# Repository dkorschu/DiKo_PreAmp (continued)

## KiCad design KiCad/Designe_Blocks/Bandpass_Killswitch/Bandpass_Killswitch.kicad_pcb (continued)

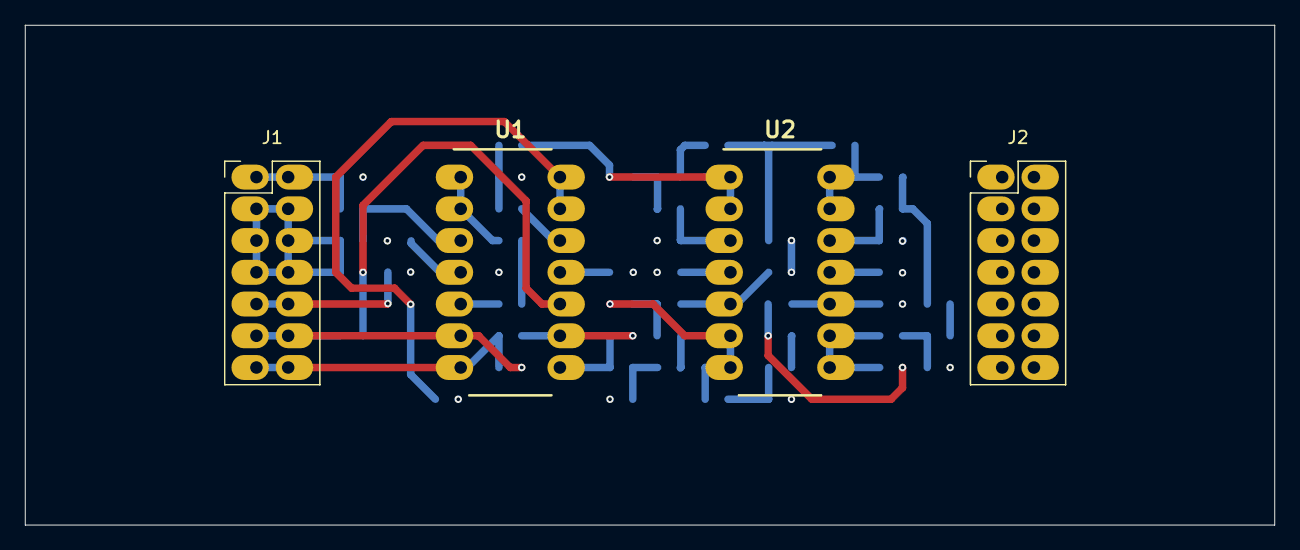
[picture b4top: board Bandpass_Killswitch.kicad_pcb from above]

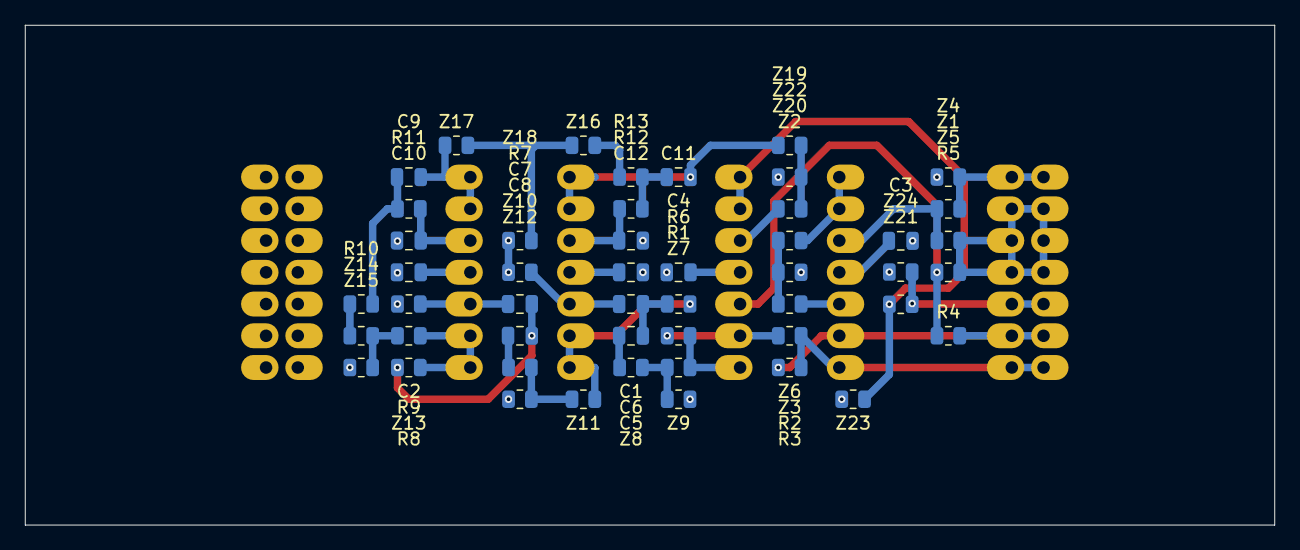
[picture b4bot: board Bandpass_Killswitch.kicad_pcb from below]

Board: 4 copper layers, 100.0 x 40.0 mm, 53 parts (49 on the bottom side), 37 nets.

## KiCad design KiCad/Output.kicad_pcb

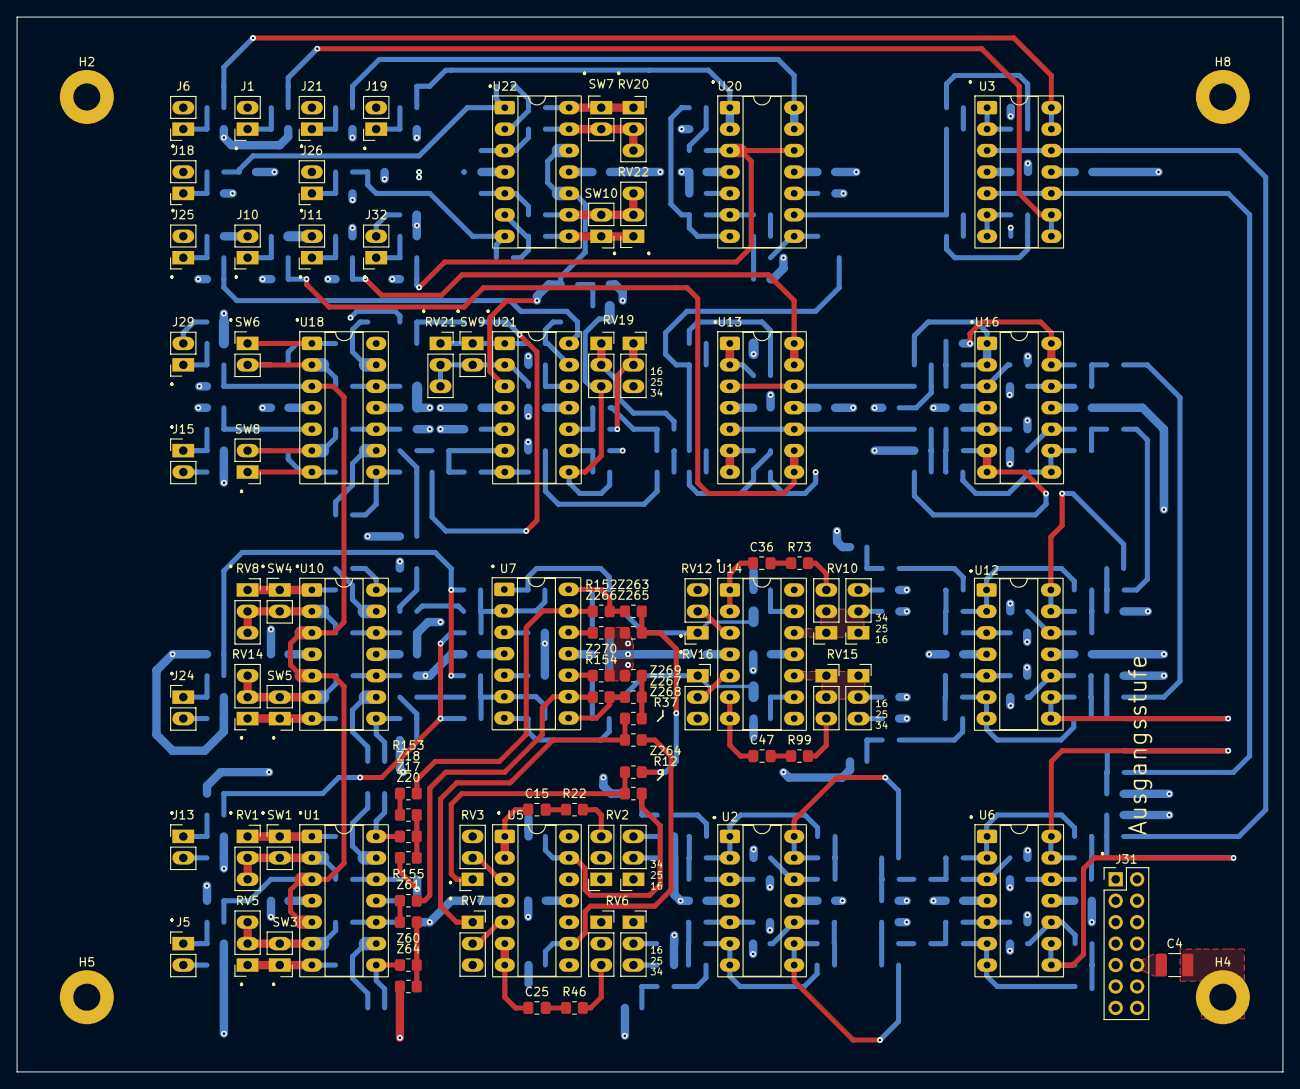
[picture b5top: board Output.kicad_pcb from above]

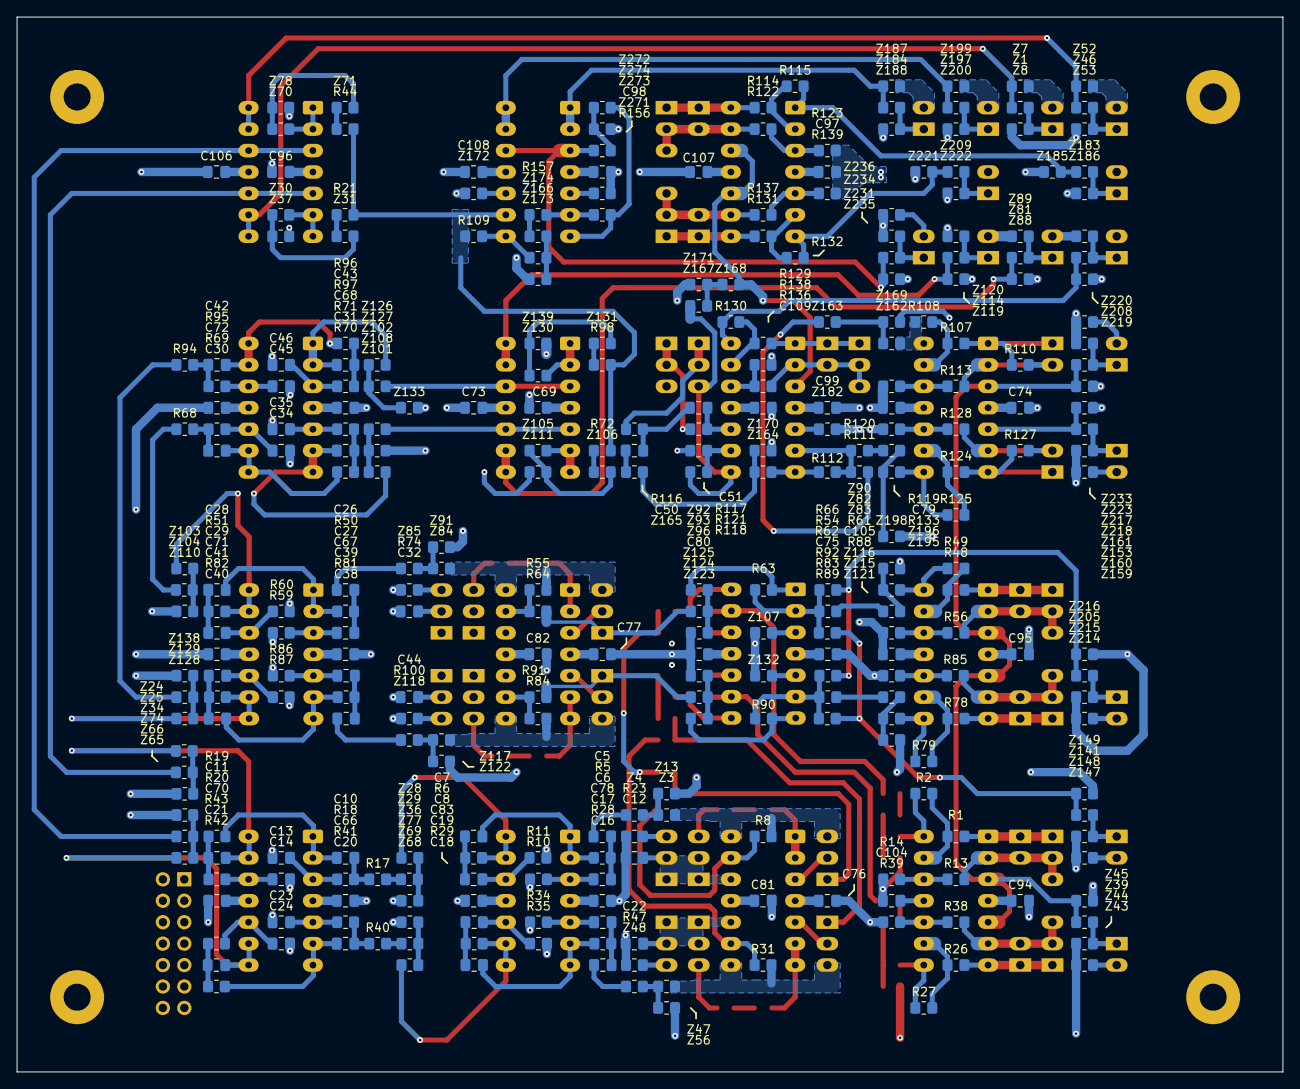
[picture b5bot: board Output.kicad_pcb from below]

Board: 4 copper layers, 150.0 x 125.0 mm, 393 parts (304 on the bottom side), 253 nets.

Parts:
C4: 10n; C_1210_3225Metric_Pad1.33x2.70mm_HandSolder
C5, C6, C7, C8, C10, C11, C13, C14, C16, C17, C18, C19, C20, C21, C23, C24, C26, C27, C28, C29, C30, C31, C34, C35, C38, C39, C40, C41, C42, C43, C45, C46: 130n; C_0805_2012Metric_Pad1.18x1.45mm_HandSolder
C12, C22, C32, C44: 470p; C_0805_2012Metric_Pad1.18x1.45mm_HandSolder
C15, C25, C36, C47: 3n; C_0805_2012Metric_Pad1.18x1.45mm_HandSolder
C50, C51: 6n8; C_0805_2012Metric_Pad1.18x1.45mm_HandSolder
C66, C67, C68, C69, C70, C71, C72, C73, C74, C75, C76, C77, C78, C79, C80, C81, C82, C83, C94, C95, C96, C97, C98, C99, C104, C105, C106, C107, C108, C109: 100n; C_0805_2012Metric_Pad1.18x1.45mm_HandSolder
H2, H5, H8: MountingHole; MountingHole_3.2mm_M3_Pad
H4: MountingHole_Pad; MountingHole_3.2mm_M3_Pad
J1: Bass_Out; PinSocket_1x02_P2.54mm_Vertical_LongPads
J5: Phono/Line_In; PinHeader_1x02_P2.54mm_Vertical_LongPads
J6: Kick_Out; PinSocket_1x02_P2.54mm_Vertical_LongPads
J10: Mid_Out; PinSocket_1x02_P2.54mm_Vertical_LongPads
J11: High_Out; PinSocket_1x02_P2.54mm_Vertical_LongPads
J13, J15, J24: Mic_Effekt_In; PinHeader_1x02_P2.54mm_Vertical_LongPads
J18: AUX_Send_1; PinSocket_1x02_P2.54mm_Vertical_LongPads
J19: Line_Out_L; PinSocket_1x02_P2.54mm_Vertical_LongPads
J21: Line_Out_R; PinSocket_1x02_P2.54mm_Vertical_LongPads
J25: AUX_Send_3; PinSocket_1x02_P2.54mm_Vertical_LongPads
J26: AUX_Send_2; PinSocket_1x02_P2.54mm_Vertical_LongPads
J29, J32: Pegel_Out; PinSocket_1x02_P2.54mm_Vertical_LongPads
J31: Conn_02x07_Odd_Even; PinHeader_2x07_P2.54mm_Vertical
R1, R26, R48, R78, R114, R129, R131: 4k7; R_0805_2012Metric_Pad1.20x1.40mm_HandSolder
R2, R21, R27, R44, R49, R54, R62, R63, R66, R72, R79, R83, R89, R90, R92, R98, R107, R108, R109, R111, R112, R115, R116, R117, R118, R120, R121, R124, R125, R130, R132, R152, R153, R154, R155, R156, R157: 10k; R_0805_2012Metric_Pad1.20x1.40mm_HandSolder
R5, R6, R10, R11, R22, R23, R28, R29, R34, R35, R46, R47, R50, R51, R59, R60, R73, R74, R81, R82, R86, R87, R99, R100: 6k8; R_0805_2012Metric_Pad1.20x1.40mm_HandSolder
R8, R12, R17, R18, R19, R20, R31, R37, R40, R41, R42, R43, R55, R64, R68, R69, R70, R71, R84, R91, R94, R95, R96, R97: 22k; R_0805_2012Metric_Pad1.20x1.40mm_HandSolder
R13, R38, R56, R85, R122, R136, R137: 470R; R_0805_2012Metric_Pad1.20x1.40mm_HandSolder
R14, R39, R61, R88, R123, R138, R139: 1k; R_0805_2012Metric_Pad1.20x1.40mm_HandSolder
R110, R113, R119, R127, R128, R133: 5k; R_0805_2012Metric_Pad1.20x1.40mm_HandSolder
RV1, RV5, RV8, RV14, RV20, RV21, RV22: 50k log; PinSocket_1x03_P2.54mm_Vertical_LongPads
RV2, RV10: 220k log; PinSocket_2x03_P2.54mm_Vertical_LongPads_Mirrored
RV3, RV7, RV12, RV16: 47k lin; PinSocket_1x03_P2.54mm_Vertical_LongPads
RV6, RV15, RV19: 220k log; PinSocket_2x03_P2.54mm_Vertical_LongPads
SW1, SW3, SW4, SW5, SW6, SW7, SW8, SW9, SW10: SW_SPDT; PinHeader_1x02_P2.54mm_Vertical_LongPads
U1, U2, U3, U5, U6, U7, U10, U12, U13, U14, U16, U18, U20, U21, U22: TL074; DIP-14_W7.62mm_Socket_LongPads
Z1, Z3, Z4, Z7, Z8, Z13, Z17, Z18, Z20, Z24, Z25, Z28, Z29, Z30, Z31, Z34, Z36, Z37, Z39, Z43, Z44, Z45, Z46, Z47, Z48, Z52, Z53, Z56, Z60, Z61, Z64, Z65, Z66, Z68, Z69, Z70, Z71, Z74, Z77, Z78, Z81, Z82, Z83, Z84, Z85, Z88, Z89, Z90, Z91, Z92, Z93, Z96, Z101, Z102, Z103, Z104, Z105, Z106, Z107, Z108, Z110, Z111, Z114, Z115, Z116, Z117, Z118, Z119, Z120, Z121, Z122, Z123, Z124, Z125, Z126, Z127, Z128, Z129, Z130, Z131, Z132, Z133, Z138, Z139, Z141, Z147, Z148, Z149, Z153, Z159, Z160, Z161, Z162, Z163, Z164, Z165, Z166, Z167, Z168, Z169, Z170, Z171, Z172, Z173, Z174, Z182, Z183, Z184, Z185, Z186, Z187, Z188, Z195, Z196, Z197, Z198, Z199, Z200, Z205, Z208, Z209, Z214, Z215, Z216, Z217, Z218, Z219, Z220, Z221, Z222, Z223, Z231, Z233, Z234, Z235, Z236, Z263, Z264, Z265, Z266, Z267, Z268, Z269, Z270, Z271, Z272, Z273, Z274: R_0805_2012Metric_Pad1.20x1.40mm_HandSolder

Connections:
9V_GND_O: J31.1, J31.2, J31.3, J31.4
+9V_O: J31.5, J31.6
+15V_O: C66.2, C67.2, C68.2, C69.2, C74.2, C75.2, C76.2, C77.2, C78.2, C94.2, C95.2, C96.2, C97.2, C98.2, C99.2, J31.13, J31.14, U1.4 (V+), U2.4 (V+), U3.4 (V+), U5.4 (V+), U6.4 (V+), U7.4 (V+), U10.4 (V+), U12.4 (V+), U13.4 (V+), U14.4 (V+), U16.4 (V+), U18.4 (V+), U20.4 (V+), U21.4 (V+), U22.4 (V+)
-15V_O: C70.2, C71.2, C72.2, C73.2, C79.2, C80.2, C81.2, C82.2, C83.2, C104.2, C105.2, C106.2, C107.2, C108.2, C109.2, J31.7, J31.8, U1.11 (V-), U2.11 (V-), U3.11 (V-), U5.11 (V-), U6.11 (V-), U7.11 (V-), U10.11 (V-), U12.11 (V-), U13.11 (V-), U14.11 (V-), U16.11 (V-), U18.11 (V-), U20.11 (V-), U21.11 (V-), U22.11 (V-)
GND_O: C4.2, C12.2, C13.1, C14.1, C22.2, C23.1, C24.1, C32.2, C34.1, C35.1, C44.2, C45.1, C46.1, C66.1, C67.1, C68.1, C69.1, C70.1, C71.1, C72.1, C73.1, C74.1, C75.1, C76.1, C77.1, C78.1, C79.1, C80.1, C81.1, C82.1, C83.1, C94.1, C95.1, C96.1, C97.1, C98.1, C99.1, C104.1, C105.1, C106.1, C107.1, C108.1, C109.1, J1.2, J6.2, J10.2, J11.2, J18.2, J19.2, J21.2, J25.2, J26.2, J31.9, J31.10, J31.11, J31.12, R10.1, R11.1, R14.1, R23.1, R34.1, R35.1, R39.1, R47.1, R59.1, R60.1, R61.1, R74.1, R86.1, R87.1, R88.1, R100.1, R119.2, R121.2, R123.2, R133.2, R138.2, R139.2, RV19.4, Z7.2, Z8.2, Z13.2, Z20.2, Z34.2, Z36.2, Z37.2, Z43.2, Z44.2, Z45.2, Z52.2, Z53.2, Z56.2, Z64.2, Z74.2, Z77.2, Z78.2, Z88.2, Z89.2, Z90.2, Z91.2, Z96.2, Z107.2, Z108.2, Z110.2, Z111.2, Z119.2, Z120.2, Z121.2, Z122.2, Z125.2, Z132.2, Z133.2, Z138.2, Z139.2, Z147.2, Z148.2, Z149.2, Z159.2, Z160.2, Z161.2, Z169.2, Z170.2, Z171.2, Z172.2, Z173.2, Z182.2, Z185.2, Z186.2, Z187.2, Z188.2, Z198.2, Z199.2, Z200.2, Z214.2, Z215.2, Z216.2, Z218.2, Z219.2, Z220.2, Z221.2, Z222.2, Z223.2, Z233.2, Z234.2, Z235.2, Z236.2, Z265.2, Z266.2, Z269.2, Z270.2, Z271.2, Z274.2
unnamed: C4.1, H4.1
unnamed: C5.1, Z4.2
unnamed: C5.2, C6.1, R5.1
unnamed: C7.2, C8.1, R6.1
unnamed: C10.1, R17.2, R18.1
unnamed: C11.1, R19.2, R20.1
unnamed: C15.1, R22.1
unnamed: C16.1, Z48.2
unnamed: C16.2, C17.1, R28.1
unnamed: C18.2, C19.1, R29.1
unnamed: C20.1, R40.2, R41.1
unnamed: C21.1, R42.2, R43.1
unnamed: C25.1, R46.1
unnamed: C26.1, Z85.2
unnamed: C26.2, C27.1, R50.1
unnamed: C28.2, C29.1, R51.1
unnamed: C30.1, R68.2, R69.1
unnamed: C31.1, R70.2, R71.1
unnamed: C36.1, R73.1
unnamed: C38.1, Z118.2
unnamed: C38.2, C39.1, R81.1
unnamed: C40.2, C41.1, R82.1
unnamed: C42.1, R94.2, R95.1
unnamed: C43.1, R96.2, R97.1
unnamed: C47.1, R99.1
unnamed: C50.1, C51.2, R116.1
unnamed: C50.2, Z165.2
unnamed: J1.1, Z1.2, Z8.1
unnamed: J5.1, Z39.1, Z44.1
unnamed: J5.2, Z43.1
unnamed: J6.1, Z46.2, Z53.1
unnamed: J10.1, Z81.2, Z89.1
unnamed: J11.1, Z114.2, Z120.1
unnamed: J13.1, Z141.1, Z148.1
unnamed: J13.2, Z147.1
unnamed: J15.1, Z153.1, Z160.1
unnamed: J15.2, Z159.1
unnamed: J18.1, Z183.2, Z186.1
unnamed: J19.1, Z184.2, Z188.1
unnamed: J21.1, Z197.2, Z200.1
unnamed: J24.1, Z205.1, Z215.1
unnamed: J24.2, Z214.1
unnamed: J25.1, Z208.2, Z220.1
unnamed: J26.1, Z209.2, Z222.1
unnamed: J29.1, Z217.2, Z223.1
unnamed: J29.2, Z233.1
unnamed: J32.1, Z231.1, Z234.1
unnamed: J32.2, Z236.1
unnamed: R2.2, U1.14, Z17.1
unnamed: R8.2, RV3.3, U5.14, Z3.1
unnamed: R12.1, RV3.1, Z264.2
unnamed: R17.1, Z29.2
unnamed: R21.1, Z31.2
unnamed: R22.2, RV2.3
unnamed: R23.2, RV2.4
unnamed: R27.2, U1.8, Z60.1
unnamed: R31.2, RV7.3, U5.8, Z47.1
unnamed: R37.1, RV7.1, Z268.2
unnamed: R40.1, Z69.2
unnamed: R44.1, Z71.2
unnamed: R46.2, RV6.3
unnamed: R47.2, RV6.4
unnamed: R49.2, U10.14, Z82.1
unnamed: R54.1, Z83.2
unnamed: R55.2, RV12.3, U14.14, Z84.1
unnamed: R62.1, R89.1, Z141.2, Z149.1
unnamed: R63.2, U7.1, Z92.1
unnamed: R64.1, RV12.1, Z93.2
unnamed: R66.1, R92.1, Z205.2, Z216.1
unnamed: R68.1, Z104.2
unnamed: R72.1, Z106.2
unnamed: R73.2, RV10.3
unnamed: R74.2, RV10.4
unnamed: R79.2, U10.8, Z115.1
unnamed: R83.1, Z116.2
unnamed: R84.2, RV16.3, U14.8, Z117.1
unnamed: R90.2, U7.7, Z123.1
unnamed: R91.1, RV16.1, Z124.2
unnamed: R94.1, Z129.2
unnamed: R98.1, Z131.2
unnamed: R99.2, RV15.3
unnamed: R100.2, RV15.4
unnamed: R108.1, U18.14, Z162.1
unnamed: R109.2, U20.8, Z166.1
unnamed: R111.2, Z163.2
unnamed: R112.1, U21.7, Z164.1
unnamed: R115.1, U22.1, Z183.1, Z185.1
unnamed: R116.2, RV19.1, RV19.2
unnamed: R117.2, RV19.5, RV19.6
unnamed: R118.1, RV19.3, U21.8, Z167.1
unnamed: R120.2, Z196.2
unnamed: R125.1, U18.8, Z195.1
unnamed: R130.1, U21.14, Z208.1, Z219.1
unnamed: R132.1, U22.7, Z209.1, Z221.1
unnamed: R152.2, U7.14, Z263.1
unnamed: R153.1, Z18.2
unnamed: R154.2, U7.8, Z267.1
unnamed: R155.1, Z61.2
unnamed: R156.1, U20.7, Z272.1
unnamed: R157.1, Z174.2
unnamed: R1.1, RV1.1, SW1.1 (A), U1.1
unnamed: R13.1, RV1.2, RV1.3, SW1.2 (B), U1.2 (-)
unnamed: R26.1, RV5.1, SW3.1 (A), U1.7
unnamed: R38.1, RV5.2, RV5.3, SW3.2 (B), U1.6 (-)
unnamed: R48.1, RV8.1, SW4.1 (A), U10.1
unnamed: R56.1, RV8.2, RV8.3, SW4.2 (B), U10.2 (-)
unnamed: R78.1, RV14.1, SW5.1 (A), U10.7
unnamed: R85.1, RV14.2, RV14.3, SW5.2 (B), U10.6 (-)
unnamed: R107.2, R110.1, SW6.1 (A), U18.1
unnamed: R110.2, R113.2, SW6.2 (B), U18.2 (-)
unnamed: R114.2, RV20.1, SW7.1 (A), U22.14
unnamed: R122.2, RV20.2, RV20.3, SW7.2 (B), U22.13 (-)
unnamed: R124.2, R127.1, SW8.1 (A), U18.7
unnamed: R127.2, R128.2, SW8.2 (B), U18.6 (-)
unnamed: R129.2, RV21.1, SW9.1 (A), U21.1
unnamed: R136.2, RV21.2, RV21.3, SW9.2 (B), U21.2 (-)
unnamed: R131.2, RV22.1, SW10.1 (A), U22.8
unnamed: R137.2, RV22.2, RV22.3, SW10.2 (B), U22.9 (-)
unnamed: R38.2, R39.2, U1.10 (+)
unnamed: R26.2, R27.1, U1.9 (-)
unnamed: R13.2, R14.2, U1.12 (+)
unnamed: R1.2, R2.1, U1.13 (-)
unnamed: C6.2, R10.2, U2.3 (+)
unnamed: C7.1, R5.2, U2.1, U2.2 (-)
unnamed: C17.2, R34.2, U2.5 (+)
unnamed: C18.1, R28.2, U2.6 (-), U2.7
unnamed: C19.2, R35.2, U2.10 (+)
unnamed: R29.2, U2.8, U2.9 (-), Z68.1
unnamed: C8.2, R11.2, U2.12 (+)
unnamed: R6.2, U2.13 (-), U2.14, Z28.1
unnamed: U3.3 (+), U3.12 (+), Z66.2
unnamed: U3.1, U3.2 (-), Z70.1
unnamed: U3.5 (+), U3.10 (+), Z25.2
unnamed: U3.6 (-), U3.7, Z30.1
unnamed: U3.8, U3.9 (-), Z1.1, Z7.1
unnamed: U3.13 (-), U3.14, Z46.1, Z52.1
unnamed: RV3.2, U5.3 (+)
unnamed: C15.2, U5.1, U5.2 (-)
unnamed: RV7.2, U5.5 (+)
unnamed: C25.2, U5.6 (-), U5.7
unnamed: C22.1, RV6.1, RV6.2, RV6.5, RV6.6, U5.10 (+)
unnamed: R31.1, R37.2, U5.9 (-)
unnamed: C12.1, RV2.1, RV2.2, RV2.5, RV2.6, U5.12 (+)
unnamed: R8.1, R12.2, U5.13 (-)
unnamed: C13.2, R18.2, U6.3 (+)
unnamed: C10.2, R19.1, U6.1, U6.2 (-)
unnamed: C23.2, R41.2, U6.5 (+)
unnamed: C20.2, R42.1, U6.6 (-), U6.7
unnamed: C24.2, R43.2, U6.10 (+)
unnamed: C21.2, U6.8, U6.9 (-), Z65.1
unnamed: C14.2, R20.2, U6.12 (+)
unnamed: C11.2, U6.13 (-), U6.14, Z24.1
unnamed: U7.3 (+), Z107.1
unnamed: R54.2, R62.2, R63.1, R66.2, U7.2 (-)
unnamed: U7.5 (+), Z132.1
unnamed: R83.2, R89.2, R90.1, R92.2, U7.6 (-)
unnamed: U7.10 (+), Z270.1
unnamed: R154.1, R155.2, U7.9 (-)
unnamed: U7.12 (+), Z266.1
unnamed: R152.1, R153.2, U7.13 (-)
unnamed: U1.3 (+), U1.5 (+), U10.3 (+), U10.5 (+), U18.3 (+), Z39.2, Z45.1, Z217.1, Z218.1
unnamed: R85.2, R88.2, U10.10 (+)
unnamed: R78.2, R79.1, U10.9 (-)
unnamed: R56.2, R61.2, U10.12 (+)
unnamed: R48.2, R49.1, U10.13 (-)
unnamed: C27.2, R59.2, U12.3 (+)
unnamed: C28.1, R50.2, U12.1, U12.2 (-)
unnamed: C39.2, R86.2, U12.5 (+)
unnamed: C40.1, R81.2, U12.6 (-), U12.7
unnamed: C41.2, R87.2, U12.10 (+)
unnamed: R82.2, U12.8, U12.9 (-), Z128.1
unnamed: C29.2, R60.2, U12.12 (+)
unnamed: R51.2, U12.13 (-), U12.14, Z103.1
unnamed: U13.3 (+), U13.12 (+), Z127.2
unnamed: U13.1, U13.2 (-), Z130.1
unnamed: U13.5 (+), U13.10 (+), Z102.2
unnamed: U13.6 (-), U13.7, Z105.1
unnamed: U13.8, U13.9 (-), Z81.1, Z88.1
unnamed: U13.13 (-), U13.14, Z114.1, Z119.1
unnamed: RV12.2, U14.3 (+)
unnamed: C36.2, U14.1, U14.2 (-)
unnamed: RV16.2, U14.5 (+)
unnamed: C47.2, U14.6 (-), U14.7
unnamed: C44.1, RV15.1, RV15.2, RV15.5, RV15.6, U14.10 (+)
unnamed: R84.1, R91.2, U14.9 (-)
unnamed: C32.1, RV10.1, RV10.2, RV10.5, RV10.6, U14.12 (+)
unnamed: R55.1, R64.2, U14.13 (-)
unnamed: C46.2, R97.2, U16.3 (+)
unnamed: C43.2, U16.1, U16.2 (-), Z126.1
unnamed: C35.2, R71.2, U16.5 (+)
unnamed: C31.2, U16.6 (-), U16.7, Z101.1
unnamed: C34.2, R69.2, U16.10 (+)
unnamed: C30.2, R70.1, U16.8, U16.9 (-)
unnamed: C45.2, R95.2, U16.12 (+)
unnamed: C42.2, R96.1, U16.13 (-), U16.14
unnamed: U18.5 (+), Z153.2, Z161.1
unnamed: R128.1, R133.1, U18.10 (+)
unnamed: R124.1, R125.2, U18.9 (-)
unnamed: R113.1, R119.1, U18.12 (+)
unnamed: R107.1, R108.2, U18.13 (-)
unnamed: U20.3 (+), U20.12 (+), Z231.2, Z235.1, Z273.2
unnamed: U20.1, U20.2 (-), Z184.1, Z187.1
unnamed: U20.5 (+), Z271.1
unnamed: R156.2, R157.2, U20.6 (-)
unnamed: U20.10 (+), Z172.1
unnamed: R21.2, R44.2, R72.2, R98.2, R109.1, U20.9 (-)
unnamed: U20.13 (-), U20.14, Z197.1, Z199.1
unnamed: U21.3 (+), U22.10 (+), U22.12 (+), Z168.2
unnamed: U21.5 (+), Z182.1
unnamed: R111.1, R112.2, R120.1, U21.6 (-)
unnamed: C51.1, R117.1, U21.10 (+)
unnamed: R118.2, R121.1, U21.9 (-)
unnamed: R136.1, R138.1, U21.12 (+)
unnamed: R129.1, R130.2, U21.13 (-)
unnamed: R122.1, R123.1, U22.3 (+)
unnamed: R114.1, R115.2, U22.2 (-)
unnamed: R137.1, R139.1, U22.5 (+)
unnamed: R131.1, R132.2, U22.6 (-)
unnamed: Z3.2, Z4.1, Z13.1
unnamed: Z17.2, Z18.1, Z20.1
unnamed: Z24.2, Z25.1, Z34.1
unnamed: Z28.2, Z29.1, Z36.1
unnamed: Z30.2, Z31.1, Z37.1
unnamed: Z47.2, Z48.1, Z56.1
unnamed: Z60.2, Z61.1, Z64.1
unnamed: Z65.2, Z66.1, Z74.1
unnamed: Z68.2, Z69.1, Z77.1
unnamed: Z70.2, Z71.1, Z78.1
unnamed: Z82.2, Z83.1, Z90.1
unnamed: Z84.2, Z85.1, Z91.1
unnamed: Z92.2, Z93.1, Z96.1
unnamed: Z101.2, Z102.1, Z108.1
unnamed: Z103.2, Z104.1, Z110.1
unnamed: Z105.2, Z106.1, Z111.1
unnamed: Z115.2, Z116.1, Z121.1
unnamed: Z117.2, Z118.1, Z122.1
unnamed: Z123.2, Z124.1, Z125.1
unnamed: Z126.2, Z127.1, Z133.1
unnamed: Z128.2, Z129.1, Z138.1
unnamed: Z130.2, Z131.1, Z139.1
unnamed: Z162.2, Z163.1, Z169.1
unnamed: Z164.2, Z165.1, Z170.1
unnamed: Z166.2, Z173.1, Z174.1
unnamed: Z167.2, Z168.1, Z171.1
unnamed: Z195.2, Z196.1, Z198.1
unnamed: Z263.2, Z264.1, Z265.1
unnamed: Z267.2, Z268.1, Z269.1
unnamed: Z272.2, Z273.1, Z274.1

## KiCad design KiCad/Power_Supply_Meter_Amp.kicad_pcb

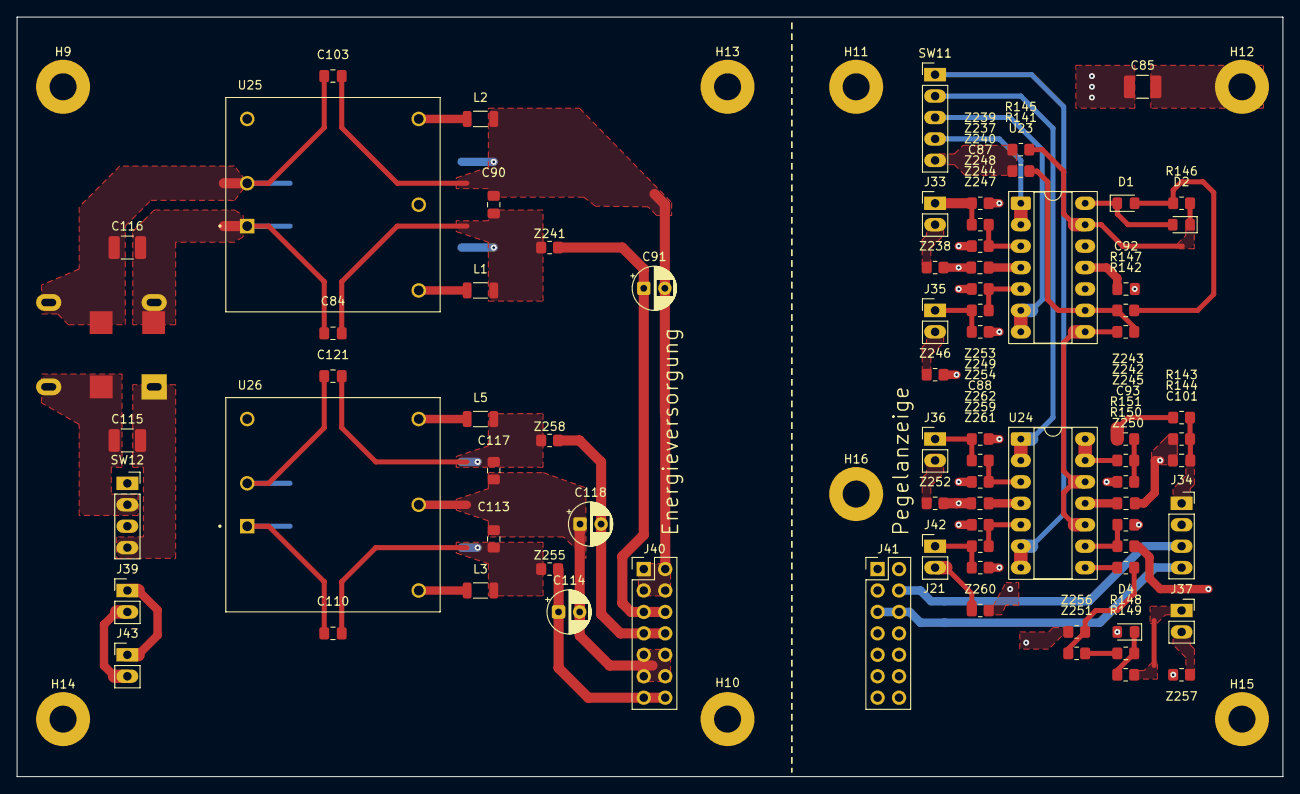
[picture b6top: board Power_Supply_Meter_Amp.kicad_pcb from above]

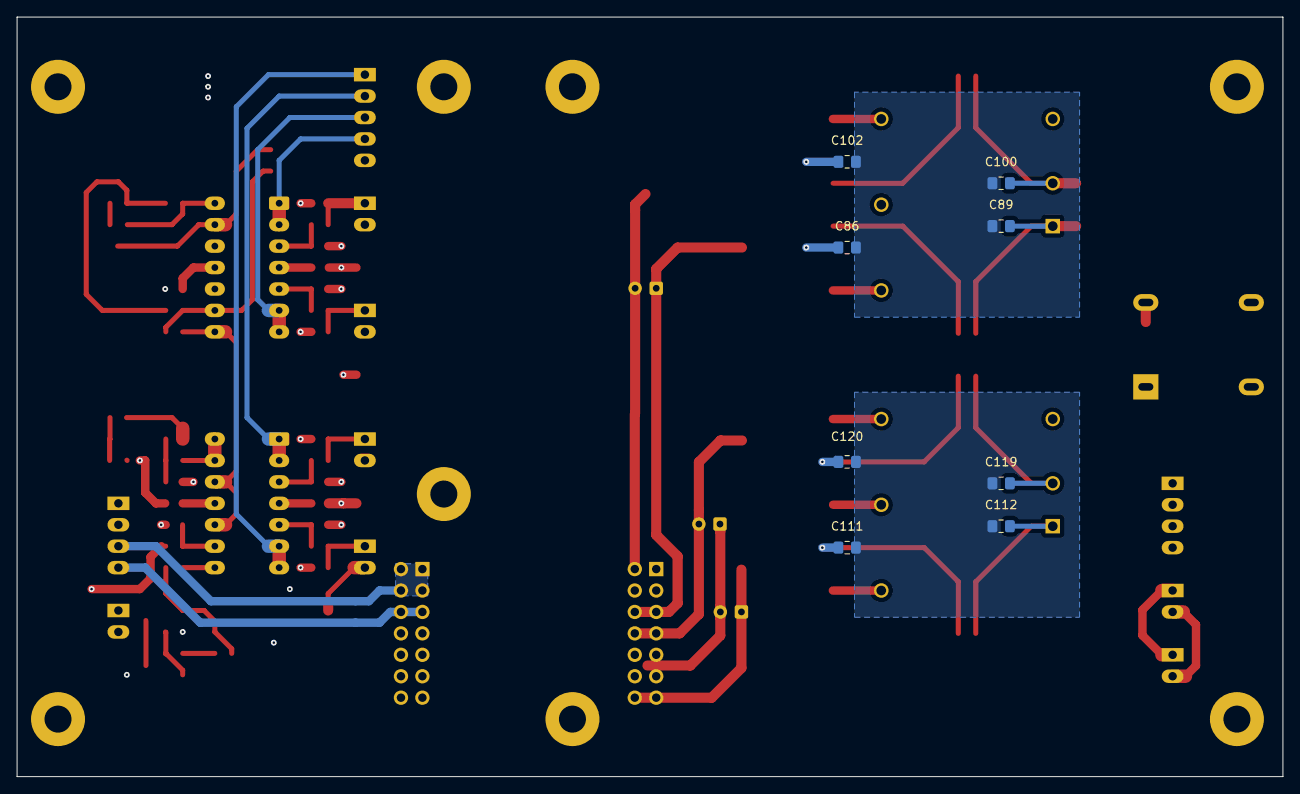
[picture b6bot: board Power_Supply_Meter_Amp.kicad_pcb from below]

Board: 4 copper layers, 150.0 x 90.0 mm, 95 parts (8 on the bottom side), 59 nets.

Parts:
C84, C103, C110, C121: 470p; C_0805_2012Metric_Pad1.18x1.45mm_HandSolder
C85: 10n; C_1210_3225Metric_Pad1.33x2.70mm_HandSolder
C86, C102, C111, C120: 1n; C_0805_2012Metric_Pad1.18x1.45mm_HandSolder
C87, C88, C90, C92, C93, C113, C117: 100n; C_0805_2012Metric_Pad1.18x1.45mm_HandSolder
C89, C100, C112, C119: 10n; C_0805_2012Metric_Pad1.18x1.45mm_HandSolder
C91, C114, C118: 10u; CP_Radial_D5.0mm_P2.50mm
C101: 4u7; C_0805_2012Metric_Pad1.18x1.45mm_HandSolder
C115, C116: 10u; C_1210_3225Metric_Pad1.33x2.70mm_HandSolder
D1, D2, D4: D; D_0805_2012Metric_Pad1.15x1.40mm_HandSolder
H9, H10, H11, H13, H14, H15, H16: MountingHole; MountingHole_3.2mm_M3_Pad
H12: MountingHole_Pad; MountingHole_3.2mm_M3_Pad
J33, J35, J36, J42: Pegel_In; PinHeader_1x02_P2.54mm_Vertical_LongPads
J34: VU_Meter_Out; PinSocket_1x04_P2.54mm_Vertical_LongPdas
J37: LED_Out; PinSocket_1x02_P2.54mm_Vertical_LongPads
J39: VCC_IN; PinHeader_1x02_P2.54mm_Vertical_LongPads
J40, J41: Conn_02x07_Odd_Even; PinHeader_2x07_P2.54mm_Vertical
J43: VCC_OUT; PinHeader_1x02_P2.54mm_Vertical_LongPads
L1, L2, L3, L5: Dämpfungsperle, 220 Ohm @ 100MHz, 0.5A; L_1206_3216Metric
L4: WE-SL575
R141: 20k; R_0805_2012Metric_Pad1.20x1.40mm_HandSolder
R142: 80k; R_0805_2012Metric_Pad1.20x1.40mm_HandSolder
R143, R144: 1k8; R_0805_2012Metric_Pad1.20x1.40mm_HandSolder
R145, R146, R149: 1k; R_0805_2012Metric_Pad1.20x1.40mm_HandSolder
R147, R148: 10k; R_0805_2012Metric_Pad1.20x1.40mm_HandSolder
R150: 12k; R_0805_2012Metric_Pad1.20x1.40mm_HandSolder
R151: 3k; R_0805_2012Metric_Pad1.20x1.40mm_HandSolder
SW11: SW_Rotary_1x4; PinHeader_1x05_P2.54mm_Vertical_LongPads
SW12: SW_DPST; PinSocket_1x04_P2.54mm_Vertical_LongPdas
U23, U24: TL074; DIP-14_W7.62mm_Socket_LongPads
U25: REC10K-2409; CONV_REC10K-2409SAW_H2
U26: REC10K-2415; CONV_REC10K-2415DAW_H2
Z237, Z238, Z239, Z240, Z241, Z242, Z243, Z244, Z245, Z246, Z247, Z248, Z249, Z250, Z251, Z252, Z253, Z254, Z255, Z256, Z257, Z258, Z259, Z260, Z261, Z262: R_0805_2012Metric_Pad1.20x1.40mm_HandSolder

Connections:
9V_GND_M: J34.3, J41.1, J41.2, J41.3, J41.4
9V_GND_P: C90.2, C91.2, C102.1, C103.2, J40.1, J40.2, J40.3, J40.4, L2.2
+9V_M: J34.4, J41.5, J41.6
+9V_P: C91.1, J40.5, J40.6, Z241.2
+15V_M: C87.2, C88.2, J41.13, J41.14, R150.1, U23.4 (V+), U24.4 (V+)
+15V_P: C114.1, J40.13, J40.14, Z255.2
-15V_M: C92.2, C93.2, J41.7, J41.8, U23.11 (V-), U24.11 (V-)
-15V_P: C118.2, J40.7, J40.8, Z258.2
/Pegel_Aux_Return: SW11.2, U24.1, U24.2 (-)
/Pegel_Mic_Effekt: SW11.3, U23.6 (-), U23.7
/Pegel_Post: SW11.1, U24.6 (-), U24.7
/Pegel_Pre: SW11.4, U23.1, U23.2 (-)
GND_9V_FILT: C86.1, C89.1, C100.2, C102.2
GND_15V_FILT: C111.1, C112.1, C119.2, C120.2
GND_M: C85.2, C87.1, C88.1, C92.1, C93.1, C101.2, D4.2 (A), J34.2, J41.9, J41.10, J41.11, J41.12, R144.1, R151.1, U23.10 (+), U23.12 (+), Z238.2, Z239.2, Z240.2, Z245.2, Z246.2, Z247.2, Z248.2, Z252.2, Z253.2, Z254.2, Z256.2, Z257.2, Z260.2, Z261.2, Z262.2
GND_P: C113.2, C114.2, C117.1, C118.1, J40.9, J40.10, J40.11, J40.12, U26.5 (COM)
unnamed: C84.2, C86.2, C90.1, L1.2, Z241.1
unnamed: C85.1, H12.1
unnamed: C110.2, C111.2, C113.1, L3.2, Z255.1
unnamed: C115.1, L4.1, SW12.4
unnamed: C115.2, L4.4, SW12.2
unnamed: C117.2, C120.1, C121.2, L5.2, Z258.1
unnamed: D1.2 (A), R146.2, R147.1
unnamed: D1.1 (K), D2.2 (A), U23.14
unnamed: D2.1 (K), R145.2, R146.1, U23.13 (-)
unnamed: D4.1 (K), R148.1, R149.2
unnamed: J33.1, Z237.1, Z239.1
unnamed: J33.2, Z238.1
unnamed: C101.1, J34.1, R143.2, R144.2
unnamed: J35.1, Z244.1, Z247.1
unnamed: J35.2, Z246.1
unnamed: J36.1, Z249.1, Z253.1
unnamed: J36.2, Z252.1
unnamed: J37.1, R149.1
unnamed: J37.2, Z257.1
unnamed: J39.1, J43.1, SW12.3
unnamed: J39.2, J43.2, SW12.1
unnamed: J42.1, Z259.1, Z261.1
unnamed: J42.2, Z260.1
unnamed: R141.1, R145.1, SW11.5
unnamed: R143.1, Z243.2
unnamed: R148.2, Z251.2
unnamed: U23.3 (+), Z237.2, Z240.1
unnamed: U23.5 (+), Z244.2, Z248.1
unnamed: R141.2, R142.1, R147.2, U23.9 (-)
unnamed: U24.8, Z250.1
unnamed: U24.3 (+), Z249.2, Z254.1
unnamed: U24.5 (+), Z259.2, Z262.1
unnamed: R142.2, U23.8, U24.10 (+), U24.12 (+)
unnamed: R150.2, R151.2, U24.9 (-)
unnamed: U24.13 (-), U24.14, Z242.1
unnamed: C84.1, C89.2, C110.1, C112.2, C116.1, L4.2, U25.1 (+VIN), U26.1 (+VIN)
unnamed: L1.1, U25.6 (+VOUT)
unnamed: C100.1, C103.1, C116.2, C119.1, C121.1, L4.3, U25.2 (-VIN), U26.2 (-VIN)
unnamed: L2.1, U25.4 (-VOUT)
unnamed: L3.1, U26.6 (+VOUT)
unnamed: L5.1, U26.4 (-VOUT)
unnamed: Z242.2, Z243.1, Z245.1
unnamed: Z250.2, Z251.1, Z256.1
